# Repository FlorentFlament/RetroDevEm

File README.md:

# RetroDevEm

RetroDevEm (Retro Device Emulator) is a free (as in Free Software)
input devices (mouse and joystick) emulator for retro consoles and
computers (Atari 2600, Atari ST, Amstrad CPC, ...).  It allows using
any input device, recognized by Linux on the Raspberry Pi, on
unmodifed retro machines.  Programs collect events from input devices
and send the corresponding signals to the console or computer.

The project consists of 2 components:
- Hardware: A daughter printed circuit board, to be plugged on a Raspberry Pi;
- Software: Programs running on the Raspberry Pi.

The daughter board can be connected to the retro machines via DB-9
flat cables.

## Project focus

This project focuses on:
- Using off the shelf hardware ;
- Devices accuracy and low latency ;
- Simplicity ;
- Low CPU usage.

## Rationale

I bought a 30 Euros Atari ST mouse adapter from a hobbyist.  It only
works with ps/2 mice and the accuracy is okish.  Especially with slow
movements, the Atari ST pointer accuracy is bad.  So why not do
something better and make it free software ?

## Project details

### Hardware

A PCB (Printed Circuit Board), with:
- 2x ULN2003AN ICs (7 Darlington transistors per IC)
- 14x 15 KOhms resistors (optional)
- 1x 40 pins socket (Raspberry Pi connector)
- 2x 10 pins headers (Atari ports connectors)

#### About the resistors

Without resistors, the design works perfectly well.  The current drawn
on the Raspberry PI GPIO pins is 706 uA, for a 440 uA current flowing
out of the Atari ST mouse/joystick port.

With 15 KOhms resistors, the design works perfectly as well.  The
current on the Raspberry Pi GPIO pins in 113 uA, for a 440 uA current
on the Atari ST port side.

#### Board wiring

| RPI sig. | J1 pin | J2/J3 pins | Atari ST signals      | Amstrad CPC sig. | Atari 2600 sig. |
|----------|--------|------------|-----------------------|------------------|-----------------|
| GPIO2    | 3      | J2 9       | P0 Right Button       | COM2 (GND Joy 2) | Pot 1 (analog)  |
| GPIO3    | 5      | J2 5       | P0 Port 0 enable      | Fire 3 (undoc)   | Pot 0 (analog)  |
| GPIO4    | 7      | J2 4       | P0 YB / Right         | Right            | Right           |
| GPIO17   | 11     | J2 3       | P0 YA / Left          | Left             | Left            |
| GPIO27   | 13     | J2 2       | P0 XA / Down          | Down             | Down            |
| GPIO22   | 15     | J2 1       | P0 XB / Up            | Up               | Up              |
| GPIO10   | 19     | J2 6       | P0 Left Button / Fire | Fire 2 (default) | Fire            |
| GPIO9    | 21     | J3 9       | P1 Right Button       |                  |                 |
| GPIO11   | 23     | J3 5       | P1 Port 0 enable      |                  |                 |
| GPIO0    | 27     | J3 4       | P1 YB / Right         |                  |                 |
| GPIO5    | 29     | J3 3       | P1 YA / Left          |                  |                 |
| GPIO6    | 31     | J3 2       | P1 XA / Down          |                  |                 |
| GPIO13   | 33     | J3 1       | P1 XB / Up            |                  |                 |
| GPIO19   | 35     | J3 6       | P1 Left Button / Fire |                  |                 |

#### Generating the gerber files

In Kicad PCB editor:
- Run the DRC (Design Rule Checker)
- File -> Fabrication outputs -> Gerbers
- Select the output directory
- Include every layer except Margin, F.Courtyard and B.Courtyard
- Keep only the following "General Options" checked:
  - Plot the reference designators
  - Check zone fills before plotting
- Keep the default "Gerber Options"
- Click "Plot" button
- Then click on "Generate Drill Files..."
- In the "Drill File Format" section, select "Gerber X2"
- Then click "Generate Drill File"
- Create a zip archive from the gerber folder.

The generated archive can be checked in Kicad's Gerber viewer.

### Software

The RetroDevEm programs need to be installed on a Raspberry Pi
connected to the Atari ST through the RetroDevEm board (an RPI
daughter board).  The programs process events from input devices
(mouse, gamepad) and send corresponding signals to the retro machine
connected to the board.

#### Prerequistes

On a fresh raspbian (Linux raspberrypi 6.12.47+rpt-rpi-v8), the
following 2 packages need to be installed: `swig`, `liblgpio-dev`,
`evtest`.

```
$ sudo apt install swig liblgpio-dev evtest
```

#### Installation

You need to create a virtualenv using the GPIO system packages on your
Raspberry Pi:

```
# mkdir -p /usr/local/venv
# python3 -m venv --system-site-packages /usr/local/venv/retrodevem
```

Then RetroDevEm can be installed in the virtual environment with pip:

```
$ source /usr/local/venv/retrodevem/bin/activate
(retrodevem) $ pip install retrodevem
Collecting retrodevem
  Downloading retrodevem-0.9-py3-none-any.whl.metadata (12 kB)
Collecting click (from retrodevem)
  Downloading click-8.3.0-py3-none-any.whl.metadata (2.6 kB)
Requirement already satisfied: gpiozero in /usr/lib/python3/dist-packages (from retrodevem) (2.0.1)
Requirement already satisfied: lgpio in /usr/lib/python3/dist-packages (from retrodevem) (0.2.2.0)
Requirement already satisfied: colorzero in /usr/lib/python3/dist-packages (from gpiozero->retrodevem) (2.0)
Downloading retrodevem-0.9-py3-none-any.whl (23 kB)
Downloading click-8.3.0-py3-none-any.whl (107 kB)
Installing collected packages: click, retrodevem
Successfully installed click-8.3.0 retrodevem-0.9
```

#### Usage

Identify the input device files using `evtest`:

```
$ evtest
No device specified, trying to scan all of /dev/input/event*
Not running as root, no devices may be available.
Available devices:
/dev/input/event0:      vc4-hdmi-0
/dev/input/event1:      vc4-hdmi-0 HDMI Jack
/dev/input/event2:      vc4-hdmi-1
/dev/input/event3:      vc4-hdmi-1 HDMI Jack
/dev/input/event4:      Sony Interactive Entertainment Wireless Controller
/dev/input/event5:      Sony Interactive Entertainment Wireless Controller Motion Sensors
/dev/input/event6:      Sony Interactive Entertainment Wireless Controller Touchpad
/dev/input/event7:      Logitech USB Optical Mouse
Select the device event number [0-7]: ^C
```

Run the `atarist-mouse` program to emulate a mouse on the Atari ST:

```
$ atarist-mouse --device /dev/input/event7 &
[1] 1947
```

Run the `atarist-joystick` program to emulate a joystick on the Atari ST:

```
$ atarist-joystick --device /dev/input/event4 &
[2] 1951
```

Available options for the `atarist-mouse` program:

```
$ atarist-mouse --help
Usage: atarist-mouse [OPTIONS]

  Send mouse events to an Atari ST connected to the RetroDevEm board.  Usage
  example: atarist-mouse --board v2.0 --device /dev/input/event0 --port 0
  --speed 4

Options:
  --board TEXT          Board revision.  [default: v2.0]
  --device TEXT         Input device to use.  [default: /dev/input/event0]
  --port INTEGER        Board/Atari port to connect the mouse to.  [default:
                        0]
  --speed INTEGER       Mouse speed divider (more = slower).  [default: 2]
  --debug / --no-debug  Display debugging information.  [default: no-debug]
  --help                Show this message and exit.
```

Available options for the `atarist-joystick` program:

```
$ atarist-joystick --help
Usage: atarist-joystick [OPTIONS]

  Send joystick/gamepad events to an Atari ST connected to the RetroDevEm
  board.  Usage example: atarist-joystick --board v2.0 --device
  /dev/input/event0 --port 0

Options:
  --board TEXT          Board revision.  [default: v2.0]
  --device TEXT         Input device to use.  [default: /dev/input/event0]
  --port INTEGER        Board/Atari ST port to connect the joystick to.
                        [default: 1]
  --debug / --no-debug  Display debugging information.  [default: no-debug]
  --help                Show this message and exit.
```

#### Starting the services with systemd

There are 2 service files in the `systemd` directory.  They need to be
updated with the appropriate device and port.  Then can be copied to
the `/etc/systemd/system` directory on the raspberry Pi.

To enable them, use `systemctl enable` and `systemctl start`.

### Additional information

- [Sourcing](file:./doc/sourcing.md)
- [Mechanical details](file:./doc/mechanical.md)

#### Consoles and computers DB9 wiring

##### Atari ST

| DB9 pins | Mouse P0            | Joystick P0            | Joystick P1 |
|----------|---------------------|------------------------|-------------|
| 1        | XB                  | Up                     | Up          |
| 2        | XA                  | Down                   | Down        |
| 3        | YA                  | Left                   | Left        |
| 4        | YB                  | Right                  | Right       |
| 5        |                     |                        | P0 enable   |
| 6        | Left But            | Fire                   | Fire        |
| 7        | +5V                 | +5V                    | +5V         |
| 8        | GND                 | GND                    | GND         |
| 9        | Right But           |                        |             |

##### Amstrad CPC & Atari 2600 Joystick

| DB9 pins | Amstrad CPC      | Atari 2600     |
|----------|------------------|----------------|
| 1        | Up               | Up             |
| 2        | Down             | Down           |
| 3        | Left             | Left           |
| 4        | Right            | Right          |
| 5        | Fire 3 (undoc)   | Pot 0 (analog) |
| 6        | Fire 2 (default) | Fire           |
| 7        | Fire 1 (extra)   | +5V            |
| 8        | COM1 (joy1)      | GND            |
| 9        | COM2 (joy2)      | Pot 1 (analog  |

Sources:
- [cpcwiki](https://www.cpcwiki.eu/index.php/Connector:Digital_joystick)
- [Atari ST Internals - page 73](https://archive.org/details/Atari_ST-Internals/page/72/mode/2up)

The first version will focus on the following use cases:
- Atari 2600: 1 joystick
- Atari ST: 1 mouse + 1 joystick
- Atari ST: 2 joysticks
- Amstrad CPC: 1 joystick

#### Schematics

## Current status

### Atari ST

- Mouse emulation is working.  Latency is below 20 ms (i.e 1 frame at
  50 Hz) and CPU usage is below 10% of a core, for normal usage.
- Joystick emulation is working.  No latency, CPU usage below 1% of a
  core.

## Todo

- Configure RPI GPIO pins to pull-down input by default;
- Write blog article about the project.
- Implement auto-fire;
- Use [python-evdev][5] instead of custom `inputdevice` module.

## Links

- [Incremental encoder on Wikipedia][4]: describes the mouse signal
  expected by the Atari ST ;
- [ATARIPiMouse Github][1]: inspiration for writing the emulator in Python ;
- [Yaumataca][2]: inspiration for the "quadrature encoder" ;
- [Atari-Quadrature-USB-Mouse-Adapter][3]

[1]:https://github.com/backofficeshow/ATARIPiMouse
[2]:https://github.com/Slamy/Yaumataca
[3]:https://github.com/jjmz/Atari-Quadrature-USB-Mouse-Adapter
[4]:https://en.wikipedia.org/wiki/Incremental_encoder
[5]:https://python-evdev.readthedocs.io/en/latest/usage.html

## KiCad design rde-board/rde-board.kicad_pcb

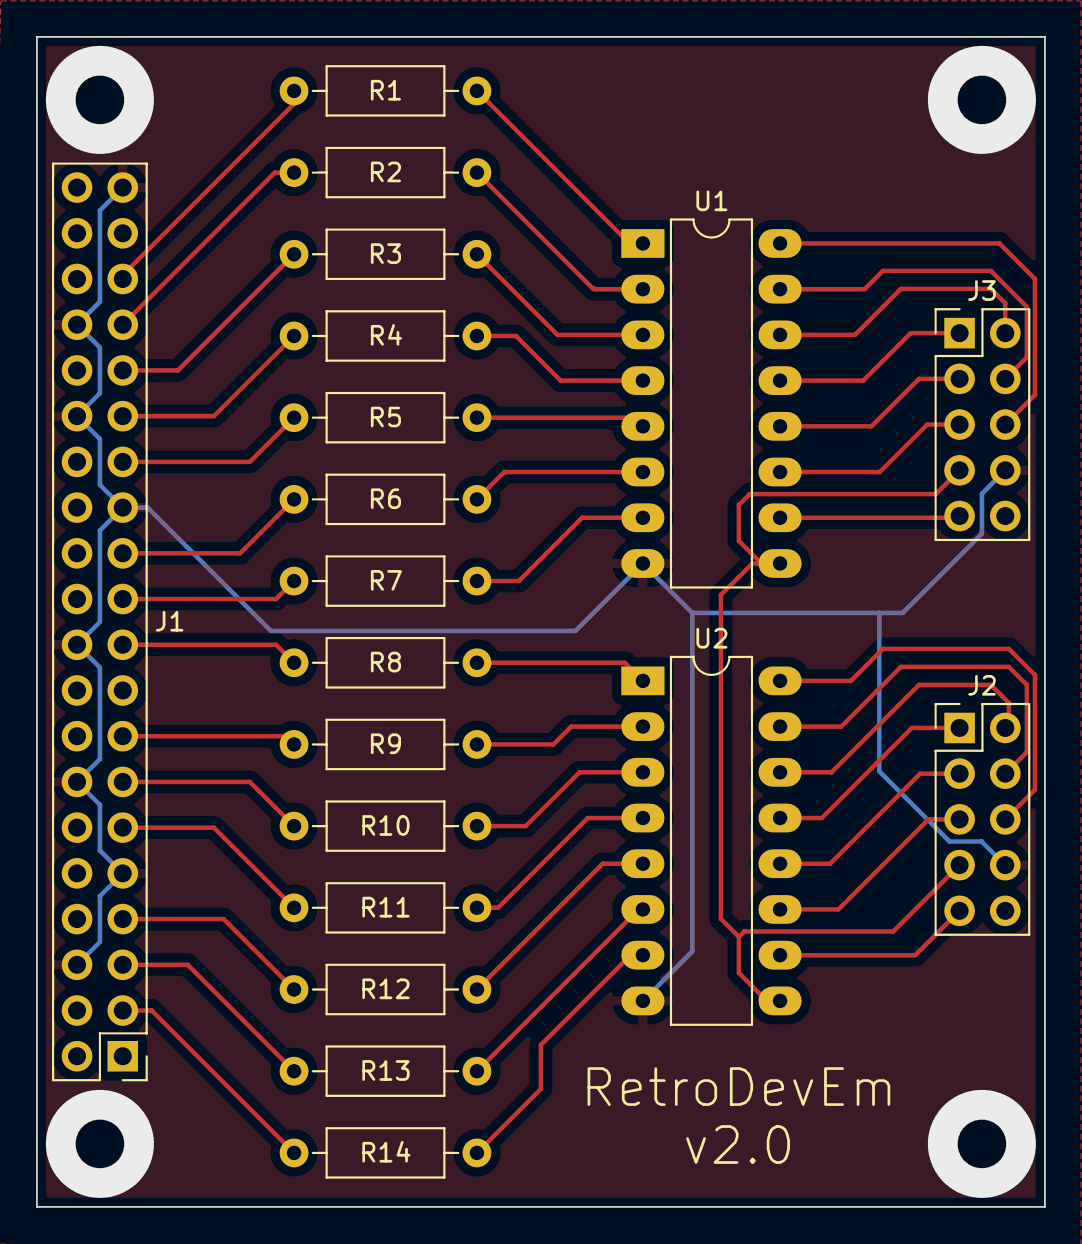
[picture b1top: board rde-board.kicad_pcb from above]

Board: 2 copper layers, 56.0 x 65.0 mm, 19 parts (0 on the bottom side), 44 nets.

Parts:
J1: RPI conn; PinHeader_2x20_P2.54mm_Vertical
J2: Mouse / Joy 1; PinHeader_2x05_P2.54mm_Vertical
J3: Joy 2; PinHeader_2x05_P2.54mm_Vertical
R1, R2, R3, R4, R5, R6, R7, R8, R9, R10, R11, R12, R13, R14: R; R_Axial_DIN0207_L6.3mm_D2.5mm_P10.16mm_Horizontal
U1, U2: ULN2003A; DIP-16_W7.62mm_LongPads

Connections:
/+5V: J2.7, J3.7, U1.9 (COM), U2.9 (COM)
GND: J1.6, J1.9, J1.14, J1.20, J1.25, J1.30, J1.34, J1.39, J2.8, J3.8, U1.8 (GND), U2.8 (GND)
unnamed: J1.3, R14.1
unnamed: J1.5, R13.1
unnamed: J1.7, R12.1
unnamed: J1.11, R11.1
unnamed: J1.13, R10.1
unnamed: J1.15, R9.1
unnamed: J1.19, R8.1
unnamed: J1.21, R7.1
unnamed: J1.23, R6.1
unnamed: J1.27, R5.1
unnamed: J1.29, R4.1
unnamed: J1.31, R3.1
unnamed: J1.33, R2.1
unnamed: J1.35, R1.1
unnamed: J2.1, U2.13 (O4)
unnamed: J2.2, U2.14 (O3)
unnamed: J2.3, U2.12 (O5)
unnamed: J2.4, U2.15 (O2)
unnamed: J2.5, U2.11 (O6)
unnamed: J2.6, U2.16 (O1)
unnamed: J2.9, U2.10 (O7)
unnamed: J3.1, U1.13 (O4)
unnamed: J3.2, U1.14 (O3)
unnamed: J3.3, U1.12 (O5)
unnamed: J3.4, U1.15 (O2)
unnamed: J3.5, U1.11 (O6)
unnamed: J3.6, U1.16 (O1)
unnamed: J3.9, U1.10 (O7)
unnamed: R1.2, U1.1 (I1)
unnamed: R2.2, U1.2 (I2)
unnamed: R3.2, U1.3 (I3)
unnamed: R4.2, U1.4 (I4)
unnamed: R5.2, U1.5 (I5)
unnamed: R6.2, U1.6 (I6)
unnamed: R7.2, U1.7 (I7)
unnamed: R8.2, U2.1 (I1)
unnamed: R9.2, U2.2 (I2)
unnamed: R10.2, U2.3 (I3)
unnamed: R11.2, U2.4 (I4)
unnamed: R12.2, U2.5 (I5)
unnamed: R13.2, U2.6 (I6)
unnamed: R14.2, U2.7 (I7)

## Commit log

2024-04-26 Add statistics
2024-04-26 Improve delay statistic - display worse over period
2024-04-26 Tune tick_period
2024-04-26 Remove unused variable, update comments
2024-04-26 Rename mouse.py to atari-mouse
    Also change indentation level from 8 to 4 spaces.
2024-04-26 Add README.md and illustration
2024-04-26 [README] Update titles levels for fit with github
2024-04-26 punctuation in README
2024-04-29 Add rde-board-v2.0
2024-04-29 Reverse YA and YB - more accuracy
2024-04-29 Add .gitignore
2024-04-29 Update README with hardware details and schematic
2024-04-29 Update rde-board
2024-04-29 Remove useless fp-info-cache file
2024-04-29 [Cleanup] Move files to folders
2024-05-02 Update hardware components
2024-05-02 Add sourcing and mechanical information
2024-05-02 Change bottom standoffs
2024-05-02 Remove 5 boards components and ugly separators
2024-05-02 [sourcing.md] Fix typo in reference
2024-05-02 Add mechanical drawings
2024-05-02 Add links to mechanical and sourcing docs
2024-05-02 [mechanical.md] Fix page formatting
2024-05-03 Update atari-mouse.py to match new design
2024-05-04 Update resistors value to 15KOhms
2024-05-04 Add 1khz-square.py to perform some tests
2024-05-04 Move inputdevice code into own module
2024-05-04 Add atari-st-joystick emulator
2024-05-05 Fix reference to ribbon cable
    Previous ribbon cable was too narrow to be clamped into the connectors.
2024-05-05 Update name of board kicad project
2024-05-05 Fix ports connectors routing on board v2.1
2024-05-07 Fix ports assignment
2024-05-13 Update README (picture + schematic)
2024-05-13 Add TODOs to README
2024-05-14 Minor README update
2024-05-15 Add support for multiple board versions to mouse emulator
2024-05-15 Add support for multiple boards and ports for joystick
    Also handles micro-disconnection.
2024-05-15 Add command line options to atari-st-mouse.py
    --board allows choosing between boards versions
    --device for selecting input device
    --xy-scale for setting the mouse scaler ratio (slowing mouse)
2024-05-15 Add command line options to atari-st-joystick
2024-05-15 Add instructions to generate Gerber files
2024-05-15 Update TODO
2024-05-15 README update
2024-05-16 Allow attaching mouse to port 1
2024-05-16 Add --debug flag
2024-05-16 Define board v2.0 for joystick
2024-05-16 Define mouse signals for board v2.1 port 1
2024-05-16 Display default values and improve help text for atari-st-joystick
2024-05-16 Document usage of the software in README
2024-05-16 Reorganize files to make programs easily installable
2024-05-16 No need for executable scripts.
    Run the modules with python -m instead
2024-05-17 Exit cleanly when running the programs on a non Raspberry Pi
2024-05-17 Add missing lgpio dependency
    Although the module is installed by default on Raspbian, we need to
    set the dependency explicitely in order to be able to run retrodevem
    in a virtualenv.
2024-05-17 Document RetroDevEm installation
2024-05-17 Update README and help message with new executable names
2024-05-17 Bump project version to 0.3
2024-05-17 Update board picture
2024-05-17 reorganise rde-board directories
    Capture board version in name of directory, so that we can have distinct board version versus software version.
2024-05-17 Fix bad looking tables in README
2024-05-17 Update pictures
2024-05-17 update pictures (with new pictures)
2024-05-23 Update standoffs sizes
2024-06-03 Minor README fix - readbility improvement
2024-06-05 Bump default board version to 2.1
2024-06-05 Enumerate possible board versions in help message
2024-06-05 Clearer error message when programs not running on a Raspberry Pi
2024-06-05 Bump version in pyproject.toml
2024-06-05 Add short options to CLI
2024-06-05 Explicit port option possible values in CLIs
2024-06-05 Bump version to 0.5
2024-06-05 Fix default port value (int -> string)
2024-06-05 Bump version to 0.6
2025-11-06 Document package dependencies + fix doc links
2025-11-08 Enable Gamepad's analog left stick
    Both the left stick and the 4 left directionnal buttons can be used to emulate the joystick's directions
2025-11-08 Fix import to allow the program to run in the development tree
2025-11-08 Bump pyproject.toml verion to 0.7
2025-11-08 Revert "Fix import to allow the program to run in the development tree"
    When installed with pip, libraries imported from the same package need to be imported from the "." package.
    This reverts commit 392107b34e837ba4f08fb2bad60b2ea305d37d5e.
2025-11-08 [pyproject.toml] Bumping from version 0.7 to 0.8
2025-11-08 Fix hat buttons not working anymore
2025-11-08 Bump to version 0.9
2025-11-08 Add systemd files + documentation update
